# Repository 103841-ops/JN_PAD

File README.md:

# JN_PAD — 12-Key Macro Pad

A compact 3×4 hot-swappable mechanical macro pad powered by the **Raspberry Pi Pico 2 (RP2350)**, designed in KiCad 7+.

---

## Features

- **12 keys** (3 columns × 4 rows matrix)
- **Hot-swappable** Kailh MX sockets — swap switches without soldering
- **Cherry MX compatible** switches (linear / tactile / clicky — user choice)
- **Raspberry Pi Pico 2 (RP2350)** microcontroller
- **KMK firmware** (CircuitPython-based, highly customisable)
- Anti-ghosting 1N4148 diodes (COL2ROW orientation)
- SMD diodes and sockets on back side (B.Cu)
- 2-layer PCB, 1.6 mm FR4
- M2 mounting holes at corners for case integration

---

## Photo / Diagram Placeholder

```
┌───────────────────────┐
│  [ SW1 ] [ SW2 ] [ SW3 ] │
│  [ SW4 ] [ SW5 ] [ SW6 ] │
│  [ SW7 ] [ SW8 ] [ SW9 ] │
│  [SW10 ] [SW11 ] [SW12 ] │
│                           │
│      [ Pico 2 ]           │
│          USB-C ↓          │
└───────────────────────┘
```

---

## Project Structure

```
JN_PAD/
├── README.md
├── firmware/
│   ├── code.py          ← KMK firmware for the macropad
│   └── boot.py          ← CircuitPython boot config
├── pcb/
│   ├── JN_PAD.kicad_pro ← KiCad 7+ project file
│   ├── JN_PAD.kicad_sch ← KiCad schematic
│   ├── JN_PAD.kicad_pcb ← KiCad PCB layout
│   └── fp-lib-table     ← Footprint library table referencing MX_V2
├── docs/
│   ├── bom.csv                 ← Bill of materials
│   ├── schematic.txt           ← Human-readable schematic description
│   └── pcb-layout-guide.txt    ← PCB layout placement guide
└── libraries/           ← Clone MX_V2 here (see Setup)
```

---

## Setup

### 1. Clone the MX_V2 Footprint Library

The PCB uses the [ai03-2725/MX_V2](https://github.com/ai03-2725/MX_V2) footprint library for hot-swap switch sockets.

```bash
git clone https://github.com/ai03-2725/MX_V2.git libraries/MX_V2
```

### 2. Copy 3D Models (Optional)

For 3D view in KiCad, copy the 3D model files:

```bash
cp -r libraries/MX_V2/3D/ pcb/
```

### 3. Open in KiCad

Open `pcb/JN_PAD.kicad_pro` in **KiCad 7 or later**.

> **Note:** The `fp-lib-table` references the MX_V2 library via  
> `${KIPRJMOD}/../libraries/MX_V2/MX_Hotswap.pretty`.  
> Make sure you have cloned the library as described above before opening the project.

---

## Firmware

### Requirements

- [CircuitPython](https://circuitpython.org/) for Raspberry Pi Pico 2
- [KMK Firmware](https://github.com/KMKfw/kmk_firmware)

### Flashing

1. **Install CircuitPython** on the Pico 2:
   - Download the Pico 2 UF2 image from [circuitpython.org](https://circuitpython.org/board/raspberry_pi_pico2/)
   - Hold BOOTSEL while plugging in USB, then drag the UF2 to the `RPI-RP2` drive.

2. **Install KMK**:
   - Download the latest KMK release from [github.com/KMKfw/kmk_firmware](https://github.com/KMKfw/kmk_firmware/releases)
   - Copy the `kmk/` folder to the root of the `CIRCUITPY` drive.

3. **Copy firmware**:
   ```bash
   cp firmware/code.py /path/to/CIRCUITPY/
   cp firmware/boot.py /path/to/CIRCUITPY/
   ```

---

## Pin Mapping

| Function | GPIO | Pico 2 Pin |
|----------|------|------------|
| COL0     | GP2  | Pin 4      |
| COL1     | GP3  | Pin 5      |
| COL2     | GP4  | Pin 6      |
| ROW0     | GP6  | Pin 9      |
| ROW1     | GP7  | Pin 10     |
| ROW2     | GP8  | Pin 11     |
| ROW3     | GP9  | Pin 12     |

---

## Bill of Materials (Summary)

| Component                  | Qty | Notes                          |
|----------------------------|-----|--------------------------------|
| Raspberry Pi Pico 2        | 1   | RP2350, mounted on B.Cu        |
| Kailh MX Hot-Swap Socket   | 12  | SMD, B.Cu                      |
| 1N4148 Diode (SOD-123)     | 12  | Anti-ghosting, SMD             |
| Pin Header 1×20 (2.54mm)   | 2   | For Pico 2 mounting            |
| Cherry MX switches         | 12  | User choice                    |
| 1U MX keycaps              | 12  | Any MX-compatible profile      |
| M2×6mm Standoffs           | 4   | PCB/case mounting              |
| M2 Screws                  | 8   | Top and bottom fastening       |

See [`docs/bom.csv`](docs/bom.csv) for the full bill of materials.

---

## License

This project is released under the [MIT License](LICENSE).

---

## Credits

- Switch footprints: [ai03-2725/MX_V2](https://github.com/ai03-2725/MX_V2) — `MX_Hotswap.pretty` / `MX_Hotswap-1U`
- Firmware: [KMKfw/kmk_firmware](https://github.com/KMKfw/kmk_firmware)

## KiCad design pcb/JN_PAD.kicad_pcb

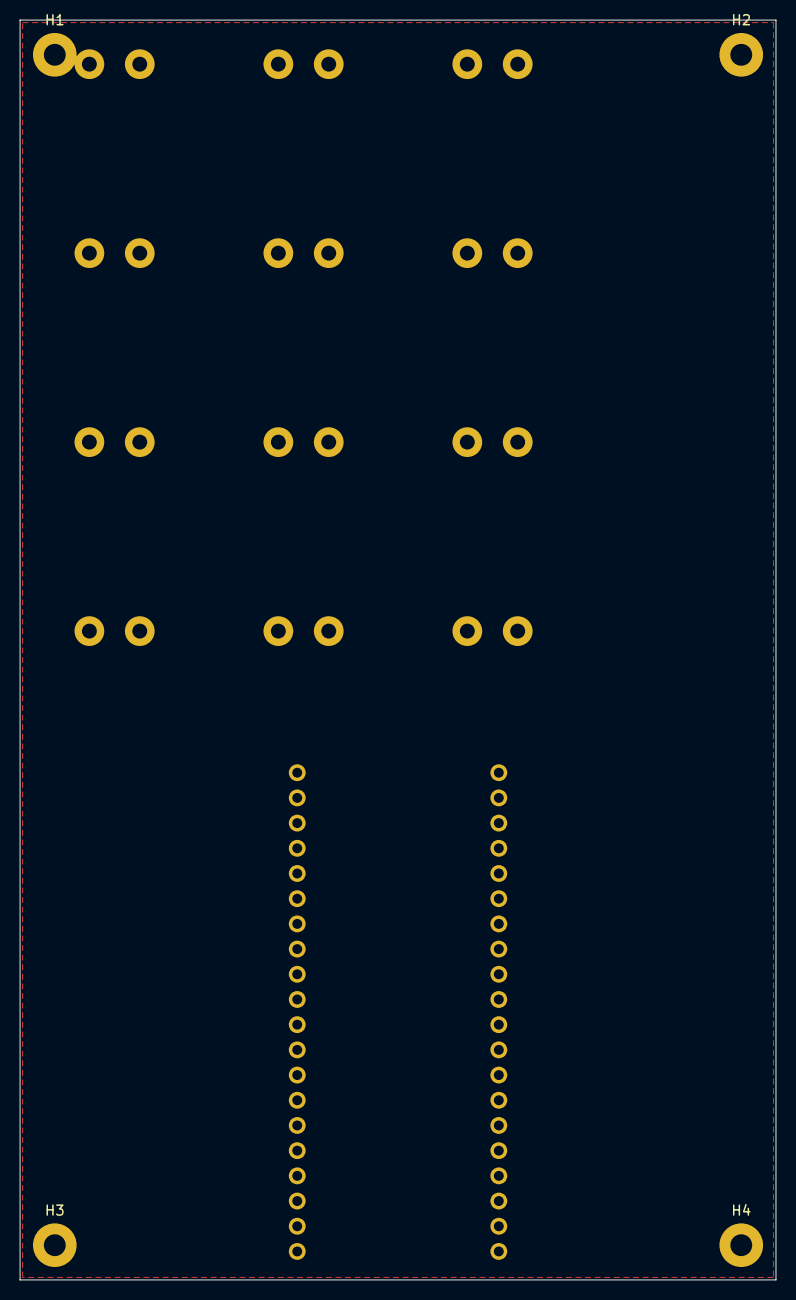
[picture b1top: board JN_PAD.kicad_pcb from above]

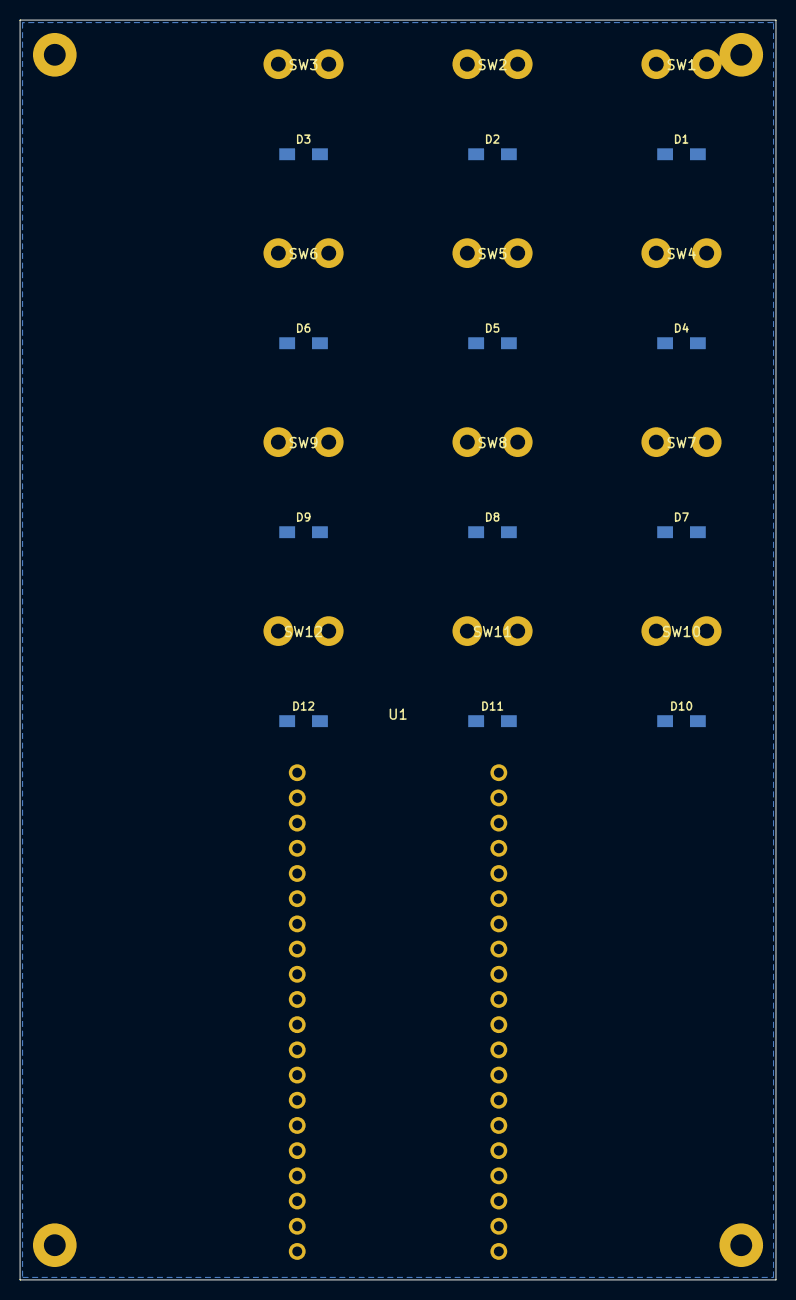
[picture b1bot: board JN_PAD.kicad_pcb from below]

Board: 2 copper layers, 76.2 x 127.0 mm, 29 parts (25 on the bottom side), 20 nets, no tracks yet.

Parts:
D1, D2, D3, D4, D5, D6, D7, D8, D9, D10, D11, D12: 1N4148; D_SOD-123
H1, H2, H3, H4: MountingHole; MountingHole_2.2mm_M2
SW1, SW2, SW3, SW4, SW5, SW6, SW7, SW8, SW9, SW10, SW11, SW12: SW_Push; MX_Hotswap-1U
U1: RPi_Pico2; RPi_Pico_SMD_TH

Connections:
COL0: SW1.1, SW4.1, SW7.1, SW10.1, U1.4
COL1: SW2.1, SW5.1, SW8.1, SW11.1, U1.5
COL2: SW3.1, SW6.1, SW9.1, SW12.1, U1.6
GND: U1.3, U1.8, U1.13, U1.18, U1.23, U1.28, U1.33, U1.38
ROW0: D1.K, D2.K, D3.K, U1.9
ROW1: D4.K, D5.K, D6.K, U1.10
ROW2: D7.K, D8.K, D9.K, U1.11
ROW3: D10.K, D11.K, D12.K, U1.12
SW1_A: D1.A, SW1.2
SW2_A: D2.A, SW2.2
SW3_A: D3.A, SW3.2
SW4_A: D4.A, SW4.2
SW5_A: D5.A, SW5.2
SW6_A: D6.A, SW6.2
SW7_A: D7.A, SW7.2
SW8_A: D8.A, SW8.2
SW9_A: D9.A, SW9.2
SW10_A: D10.A, SW10.2
SW11_A: D11.A, SW11.2
SW12_A: D12.A, SW12.2

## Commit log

2026-02-26 Initial plan
2026-02-26 Create complete JN_PAD KiCad PCB project from scratch
